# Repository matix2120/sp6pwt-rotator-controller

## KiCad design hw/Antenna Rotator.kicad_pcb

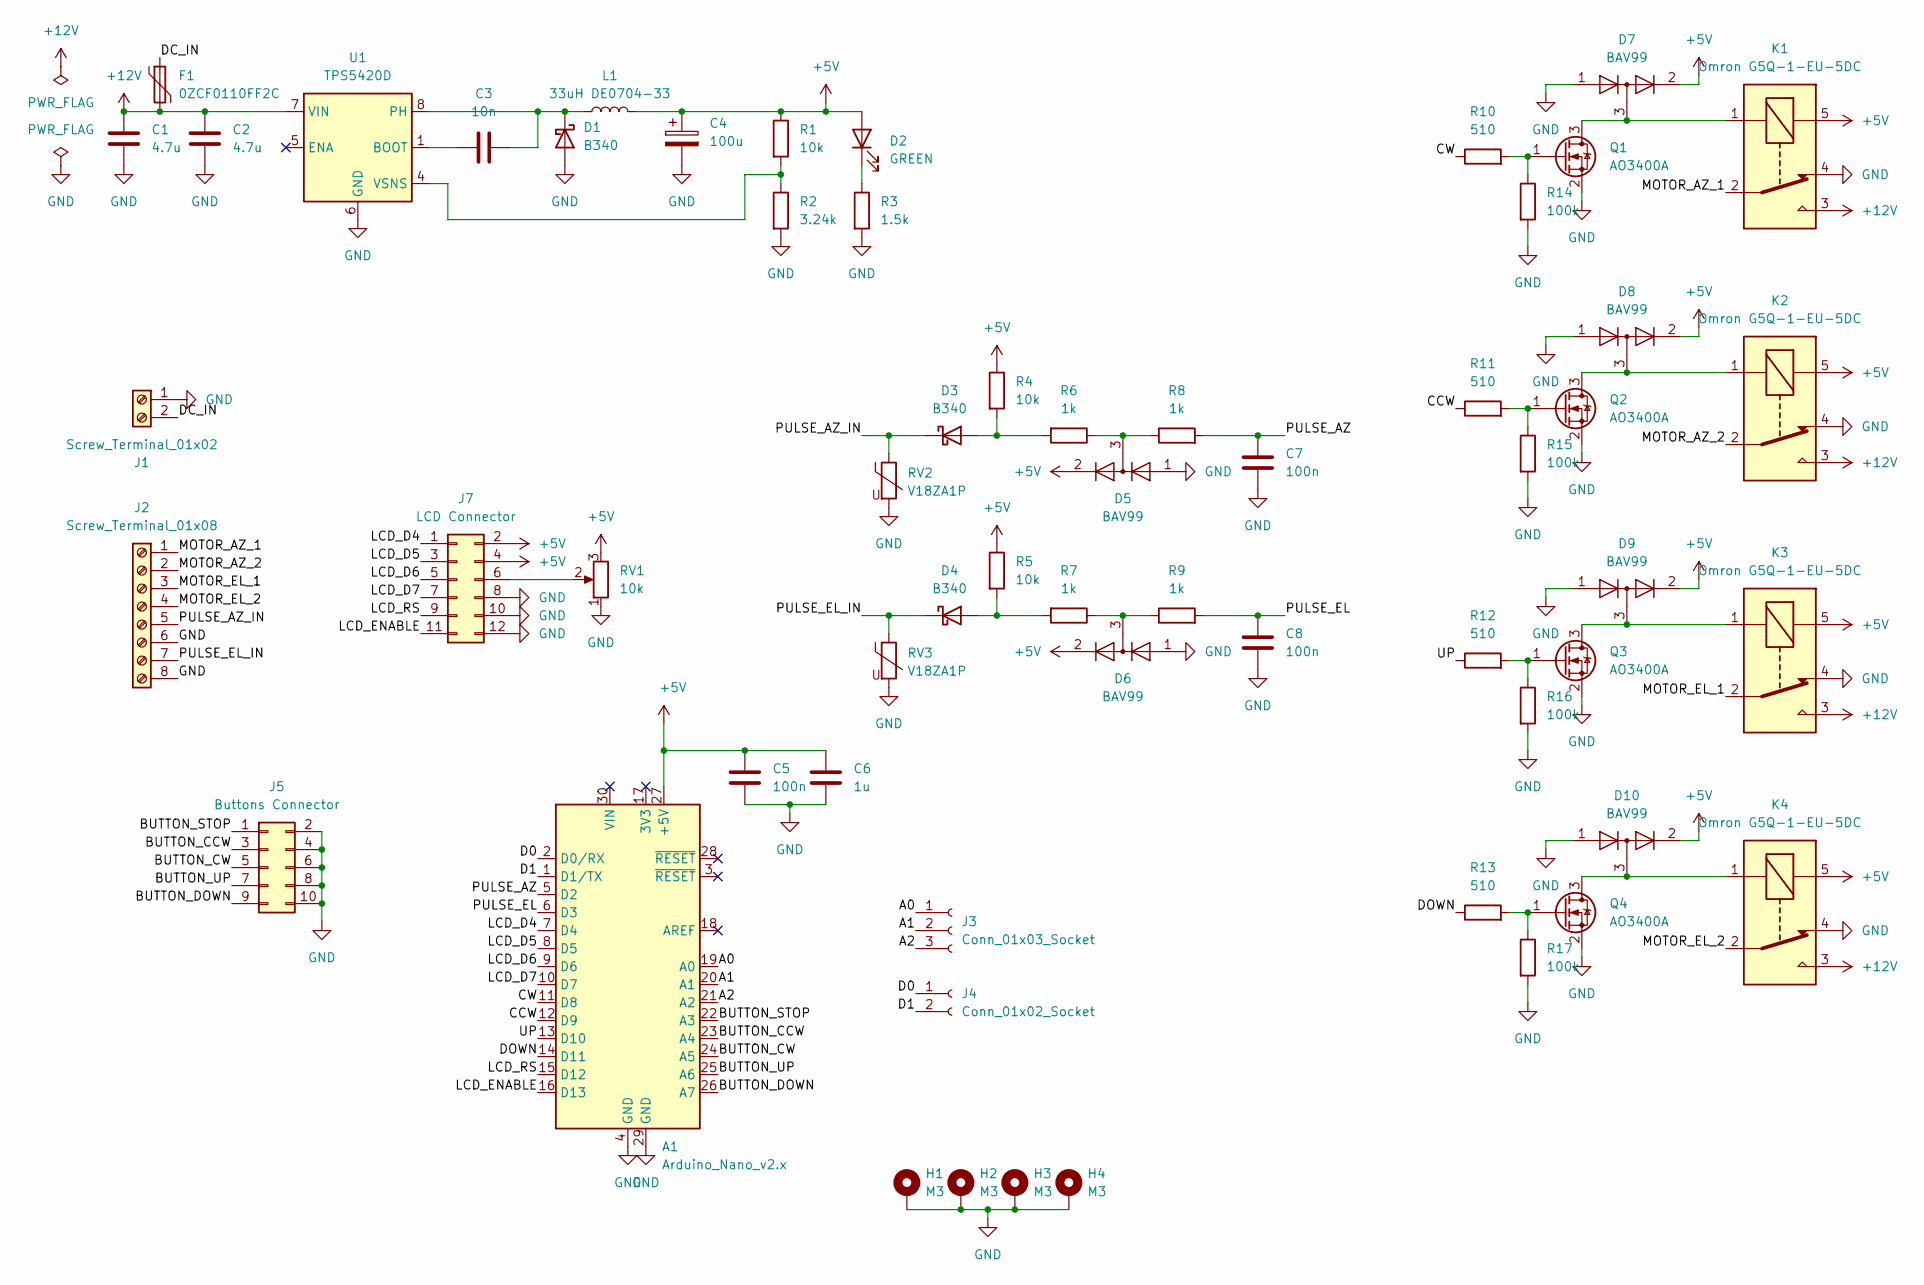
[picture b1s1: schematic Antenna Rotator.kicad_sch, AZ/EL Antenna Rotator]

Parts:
A1: Arduino_Nano_v2.x; Arduino_Nano
C1, C2: 4.7u; C_0805_2012Metric_Pad1.18x1.45mm_HandSolder
C3: 10n; C_0805_2012Metric_Pad1.18x1.45mm_HandSolder
C4: 100u; CP_Elec_6.3x5.4
C5, C7, C8: 100n; C_0805_2012Metric_Pad1.18x1.45mm_HandSolder
C6: 1u; C_0805_2012Metric_Pad1.18x1.45mm_HandSolder
D1, D3, D4: B340; D_SMA-SMB_Universal_Handsoldering
D2: GREEN; LED_0805_2012Metric_Pad1.15x1.40mm_HandSolder
D5, D6, D7, D8, D9, D10: BAV99; SOT-23
F1: 0ZCF0110FF2C; Fuse_2920_7451Metric_Pad2.10x5.45mm_HandSolder
H1, H2, H3, H4: M3; MountingHole_3.2mm_M3_Pad
J1: Screw_Terminal_01x02; TerminalBlock_bornier-2_P5.08mm
J2: Screw_Terminal_01x08; TerminalBlock_bornier-8_P5.08mm
J3: Conn_01x03_Socket; PinSocket_1x03_P2.54mm_Vertical
J4: Conn_01x02_Socket; PinSocket_1x02_P2.54mm_Vertical
J5: Buttons Connector; PinSocket_2x05_P2.54mm_Vertical
J7: LCD Connector; PinSocket_2x06_P2.54mm_Vertical
K1, K2, K3, K4: Omron G5Q-1-EU-5DC; Relay_SPDT_Omron-G5Q-1
L1: 33uH DE0704-33; L_7.3x7.3_H4.5
Q1, Q2, Q3, Q4: AO3400A; SOT-23
R1, R4, R5: 10k; R_0805_2012Metric_Pad1.20x1.40mm_HandSolder
R2: 3.24k; R_0805_2012Metric_Pad1.20x1.40mm_HandSolder
R3: 1.5k; R_0805_2012Metric_Pad1.20x1.40mm_HandSolder
R6, R7, R8, R9: 1k; R_0805_2012Metric_Pad1.20x1.40mm_HandSolder
R10, R11, R12, R13: 510; R_0805_2012Metric_Pad1.20x1.40mm_HandSolder
R14, R15, R16, R17: 100k; R_0805_2012Metric_Pad1.20x1.40mm_HandSolder
RV1: 10k; Potentiometer_Piher_PT-10-V05_Vertical
RV2, RV3: V18ZA1P; RV_Disc_D7mm_W3.4mm_P5mm
U1: TPS5420D; SOIC-8_3.9x4.9mm_P1.27mm

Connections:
+5V: A1.27 (+5V), C4.1, C5.2, C6.1, D2.2 (A), D5.2 (A), D6.2 (A), D7.2 (A), D8.2 (A), D9.2 (A), D10.2 (A), J7.2, J7.4, K1.5, K2.5, K3.5, K4.5, L1.2, R1.1, R4.1, R5.1, RV1.3
+12V: C1.1, C2.1, F1.2, K1.3, K2.3, K3.3, K4.3, U1.7 (VIN)
/A0: A1.19 (A0), J3.1
/A1: A1.20 (A1), J3.2
/A2: A1.21 (A2), J3.3
/BUTTON_CCW: A1.23 (A4), J5.3
/BUTTON_CW: A1.24 (A5), J5.5
/BUTTON_DOWN: A1.26 (A7), J5.9
/BUTTON_STOP: A1.22 (A3), J5.1
/BUTTON_UP: A1.25 (A6), J5.7
/CCW: A1.12 (D9), R11.1
/CW: A1.11 (D8), R10.1
/D0: A1.2 (D0/RX), J4.1
/D1: A1.1 (D1/TX), J4.2
/DC_IN: F1.1, J1.2
/DOWN: A1.14 (D11), R13.1
/LCD_D4: A1.7 (D4), J7.1
/LCD_D5: A1.8 (D5), J7.3
/LCD_D6: A1.9 (D6), J7.5
/LCD_D7: A1.10 (D7), J7.7
/LCD_ENABLE: A1.16 (D13), J7.11
/LCD_RS: A1.15 (D12), J7.9
/MOTOR_AZ_1: J2.1, K1.2
/MOTOR_AZ_2: J2.2, K2.2
/MOTOR_EL_1: J2.3, K3.2
/MOTOR_EL_2: J2.4, K4.2
/PULSE_AZ: A1.5 (D2), C7.1, R8.2
/PULSE_AZ_IN: D3.1 (K), J2.5, RV2.1
/PULSE_EL: A1.6 (D3), C8.1, R9.2
/PULSE_EL_IN: D4.1 (K), J2.7, RV3.1
/UP: A1.13 (D10), R12.1
GND: A1.4 (GND), A1.29 (GND), C1.2, C2.2, C4.2, C5.1, C6.2, C7.2, C8.2, D1.2 (A), D5.1 (K), D6.1 (K), D7.1 (K), D8.1 (K), D9.1 (K), D10.1 (K), H1.1, H2.1, H3.1, H4.1, J1.1, J2.6, J2.8, J5.2, J5.4, J5.6, J5.8, J5.10, J7.8, J7.10, J7.12, K1.4, K2.4, K3.4, K4.4, Q1.2 (S), Q2.2 (S), Q3.2 (S), Q4.2 (S), R2.2, R3.2, R14.2, R15.2, R16.2, R17.2, RV1.1, RV2.2, RV3.2, U1.6 (GND)
unnamed: C3.2, D1.1 (K), L1.1, U1.8 (PH)
unnamed: D2.1 (K), R3.1
unnamed: D3.2 (A), R4.2, R6.2
unnamed: D4.2 (A), R5.2, R7.2
unnamed: D5.3 (K), R6.1, R8.1
unnamed: D6.3 (K), R7.1, R9.1
unnamed: J7.6, RV1.2
unnamed: D7.3 (K), K1.1, Q1.3 (D)
unnamed: Q1.1 (G), R10.2, R14.1
unnamed: D8.3 (K), K2.1, Q2.3 (D)
unnamed: Q2.1 (G), R11.2, R15.1
unnamed: D9.3 (K), K3.1, Q3.3 (D)
unnamed: Q3.1 (G), R12.2, R16.1
unnamed: D10.3 (K), K4.1, Q4.3 (D)
unnamed: Q4.1 (G), R13.2, R17.1
unnamed: C3.1, U1.1 (BOOT)
unnamed: R1.2, R2.1, U1.4 (VSNS)

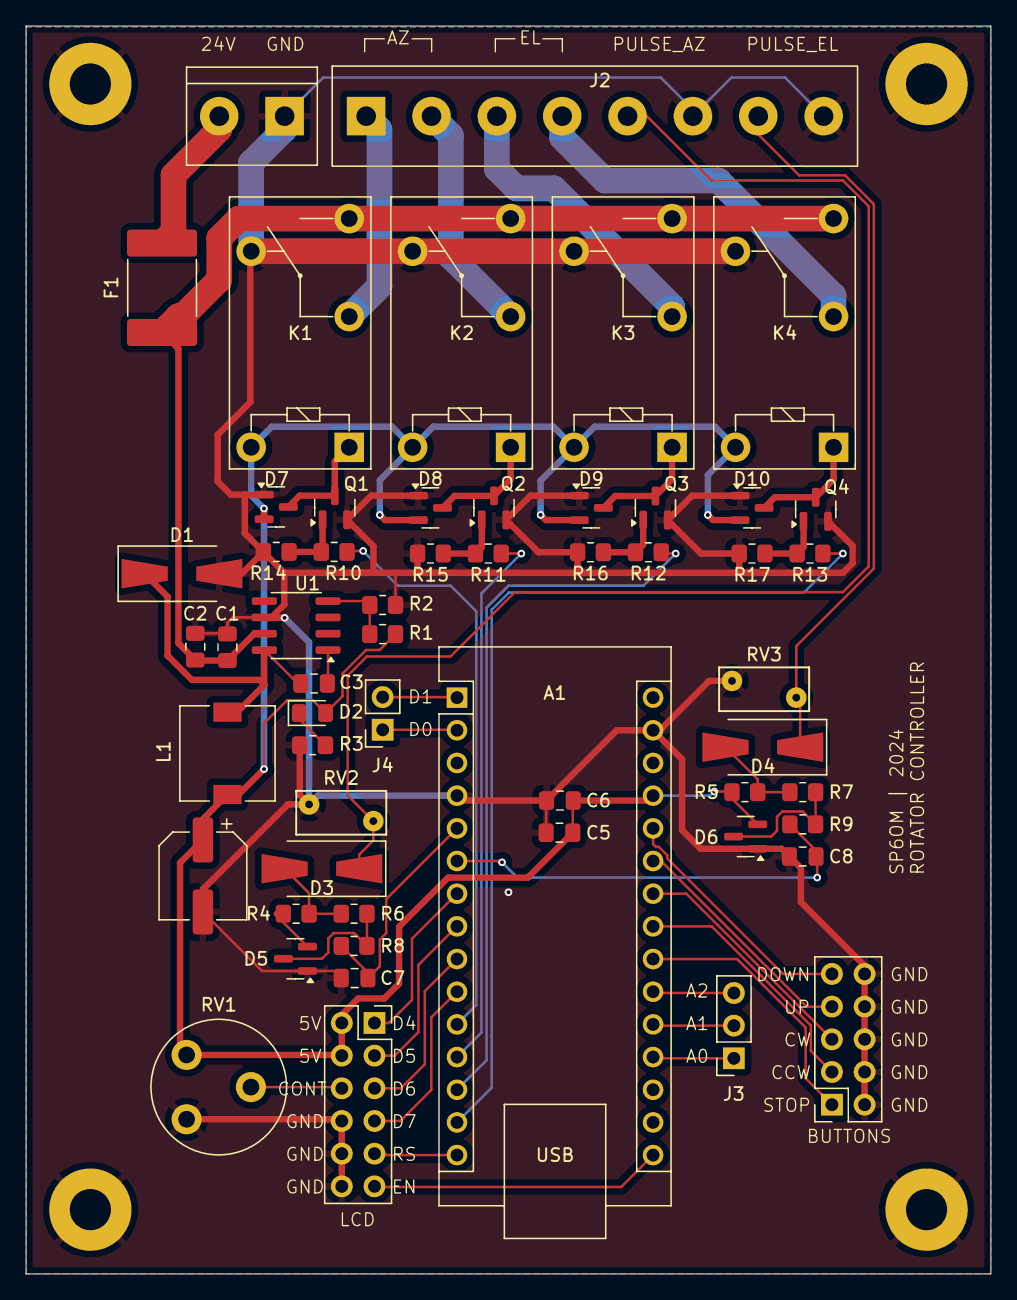
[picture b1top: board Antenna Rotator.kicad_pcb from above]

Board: 2 copper layers, 75.0 x 97.0 mm, 60 parts (0 on the bottom side), 49 nets.

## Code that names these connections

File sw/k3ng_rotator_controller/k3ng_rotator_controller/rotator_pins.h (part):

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/* azimuth pins --------------------- (use just the azimuth pins for an azimuth-only rotator) */

#define rotate_cw 8              // goes high to activate rotator R (CW) rotation - pin 1 on Yaesu connector
#define rotate_ccw 9             // goes high to activate rotator L (CCW) rotation - pin 2 on Yaesu connector
#define rotate_cw_ccw  0         // goes high for both CW and CCW rotation
#define rotate_cw_pwm 0          // optional - PWM CW output - set to 0 to disable (must be PWM capable pin)
#define rotate_ccw_pwm 0         // optional - PWM CCW output - set to 0 to disable (must be PWM capable pin)
#define rotate_cw_ccw_pwm 0      // optional - PWM on CW and CCW output - set to 0 to disable (must be PWM capable pin)
#define rotate_cw_freq 0         // optional - CW variable frequency output
#define rotate_ccw_freq 0        // optional - CCW variable frequency output
#define button_cw A5              // normally open button to ground for manual CW rotation (schematic pin: A2)
#define button_ccw A4             // normally open button to ground for manual CCW rotation (schematic pin: A3)
#define serial_led 0             // LED blinks when command is received on serial port (set to 0 to disable)
#define rotator_analog_az 0     // reads analog azimuth voltage from rotator - pin 4 on Yaesu connector
#define azimuth_speed_voltage 0  // optional - PWM output for speed control voltage feed into rotator (on continually unlike rotate_cw_pwm and rotate_ccw_pwm)
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#define az_speed_pot 0           // connect to wiper of 1K to 10K potentiometer for speed control (set to 0 to disable)
#define az_preset_pot 0          // connect to wiper of 1K to 10K potentiometer for preset control (set to 0 to disable)
#define preset_start_button 0    // connect to momentary switch (ground on button press) for preset start (set to 0 to disable or for preset automatic start)
#define button_stop A3            // connect to momentary switch (ground on button press) for preset stop (set to 0 to disable or for preset automatic start)
#define rotation_indication_pin 0
#define blink_led 0
#define az_stepper_motor_pulse 0
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  #define rotate_up_freq 0          // optional - UP variable frequency output
  #define rotate_down_freq 0        // optional - UP variable frequency output
  #define rotator_analog_el 0      // reads analog elevation voltage from rotator
  #define button_up A6               // normally open button to ground for manual up elevation
  #define button_down A7             // normally open button to ground for manual down rotation
  #define brake_el 0                // goes high to disengage elevation brake (set to 0 to disable)
  #define elevation_speed_voltage  0 // optional - PWM output for speed control voltage feed into rotator (on continually unlike rotate_up_pwm and rotate_down_pwm)
  #define el_stepper_motor_pulse 0
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// rotary encoder pins and options
#ifdef FEATURE_AZ_PRESET_ENCODER 
  #define az_rotary_preset_pin1 0                     // CW Encoder Pin
  #define az_rotary_preset_pin2 0                     // CCW Encoder Pin
#endif //FEATURE_AZ_PRESET_ENCODER

#ifdef FEATURE_EL_PRESET_ENCODER 
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
#if defined(FEATURE_AZ_POSITION_ROTARY_ENCODER) || defined(FEATURE_AZ_POSITION_ROTARY_ENCODER_USE_PJRC_LIBRARY)
  #define az_rotary_position_pin1 0                     // CW Encoder Pin
  #define az_rotary_position_pin2 0                     // CCW Encoder Pin
#endif //FEATURE_AZ_POSITION_ROTARY_ENCODER

#if defined(FEATURE_EL_POSITION_ROTARY_ENCODER) || defined(FEATURE_EL_POSITION_ROTARY_ENCODER_USE_PJRC_LIBRARY)
  #define el_rotary_position_pin1 0                     // CW Encoder Pin
  #define el_rotary_position_pin2 0                     // CCW Encoder Pin
#endif //FEATURE_EL_POSITION_ROTARY_ENCODER

#ifdef FEATURE_AZ_POSITION_PULSE_INPUT
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
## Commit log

2024-11-13 Add PCB design
2024-11-13 Add enclosure 3D model
2024-11-13 Add base firmware
    Add 1:1 copy of k3ng_rotator_controller repo in version 2023.10.02.2200
2024-11-13 Add changes AZ/EL
2024-12-21 Fix AZ/EL controller on Arduino Nano Every
    - Fix interrupts,
    - set start AZ value to 0,
    - enable limits,
    - change pulses resolution to 1 pulse / 1 degree.
